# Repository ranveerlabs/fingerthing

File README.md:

# fingerthing

i wanted touchid but not a mac

USB fingerprint security key. npm 2FA first, other FIDO2 sites too.

Pico 2 + pico-fido2 first. UART fingerprint sensor next, then a custom RP2350
board and case. Nothing tested on hardware yet.

[build](firmware/README.md) · [hardware](hardware/DESIGN.md) · [journal](JOURNAL.md)

Targets: Linux, Windows, macOS and [FreeBSD](host/freebsd/README.md).

[AGPL-3.0-only](LICENSE)

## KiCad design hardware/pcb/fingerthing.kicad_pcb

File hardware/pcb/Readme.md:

# pcb

KiCad 10. 34 x 48 mm, four layers, rounded corners. RP2350A, USB-C, R503 header,
GP6 presence button and rear SWD connector. All nets are routed. ERC, DRC and
board/schematic parity pass with no exclusions.

USB targets 90 ohms on JLC04161H-7628. The coupled section uses 0.235 mm traces,
0.15 mm spacing and 0.25 mm clearance to the ground fill. JLCPCB's calculator
returned 0.2347 mm for those inputs on 2026-10-04.

Copper and dielectric thicknesses follow that stackup: 0.035 mm outer copper,
0.0152 mm inner copper, 0.2104 mm prepreg and a 1.065 mm core. Solder-mask and
material-property fields remain nominal. Connector joins and ESD fan-out are
not fully coupled. Final fabrication review and hardware testing remain.

J1 is JAE DX07S016JA1R1500. The local KiCad footprint grounds both shell
reinforcement pads and removes the edge silk markers. Flash, crystal and core
regulator routing come from Raspberry Pi's RP2350A R4/S1 reference. C20 adds a
100 nF VBUS bypass beside the ESD protector's supply via.

R503 cable fit and the enclosure are not confirmed. Do not order this yet.
`bash hardware/check.sh` runs ERC and DRC with KiCad's standard libraries installed.

[BOM](bom.csv): 47 fitted components. R1 is DNP. U2 is AP2112K-3.3TRG1,
with C1 and C5 beside its input and output. Suspend handling and current
measurements remain, see [power](../power.md).

U5 is TPS22919DCKR. GP8 switches both R503 supplies. C21 bypasses the input,
C22 bypasses the output, R15 pulls ON down and R16 pulls sensor RX up to the
switched rail. The `pcb` and `enroll-pcb` images control the switch, with physical
power and backfeed tests still pending.
The UART pull-up branch uses In1.Cu below the USB routing.

The [local switch symbol](fingerthing.kicad_sym) comes from KiCad's
[Power_Management library](https://gitlab.com/kicad/libraries/kicad-symbols/-/blob/master/Power_Management.kicad_sym).
QOD has a passive pin type because TI specifies tying it to OUT. [license](LICENSE.kicad)

[reference](https://datasheets.raspberrypi.com/rp2350/Minimal-KiCAD.zip) · [license](LICENSE.raspberrypi)

[USB footprint](https://gitlab.com/kicad/libraries/kicad-footprints/-/blob/master/Connector_USB.pretty/USB_C_Receptacle_JAE_DX07S016JA1R1500.kicad_mod) · [license](LICENSE.kicad)

[impedance calculator](https://jlcpcb.com/pcb-impedance-calculator) · [stackup](https://jlcpcb.com/impedance) · [ESD layout](https://www.st.com/resource/en/datasheet/usblc6-2.pdf)

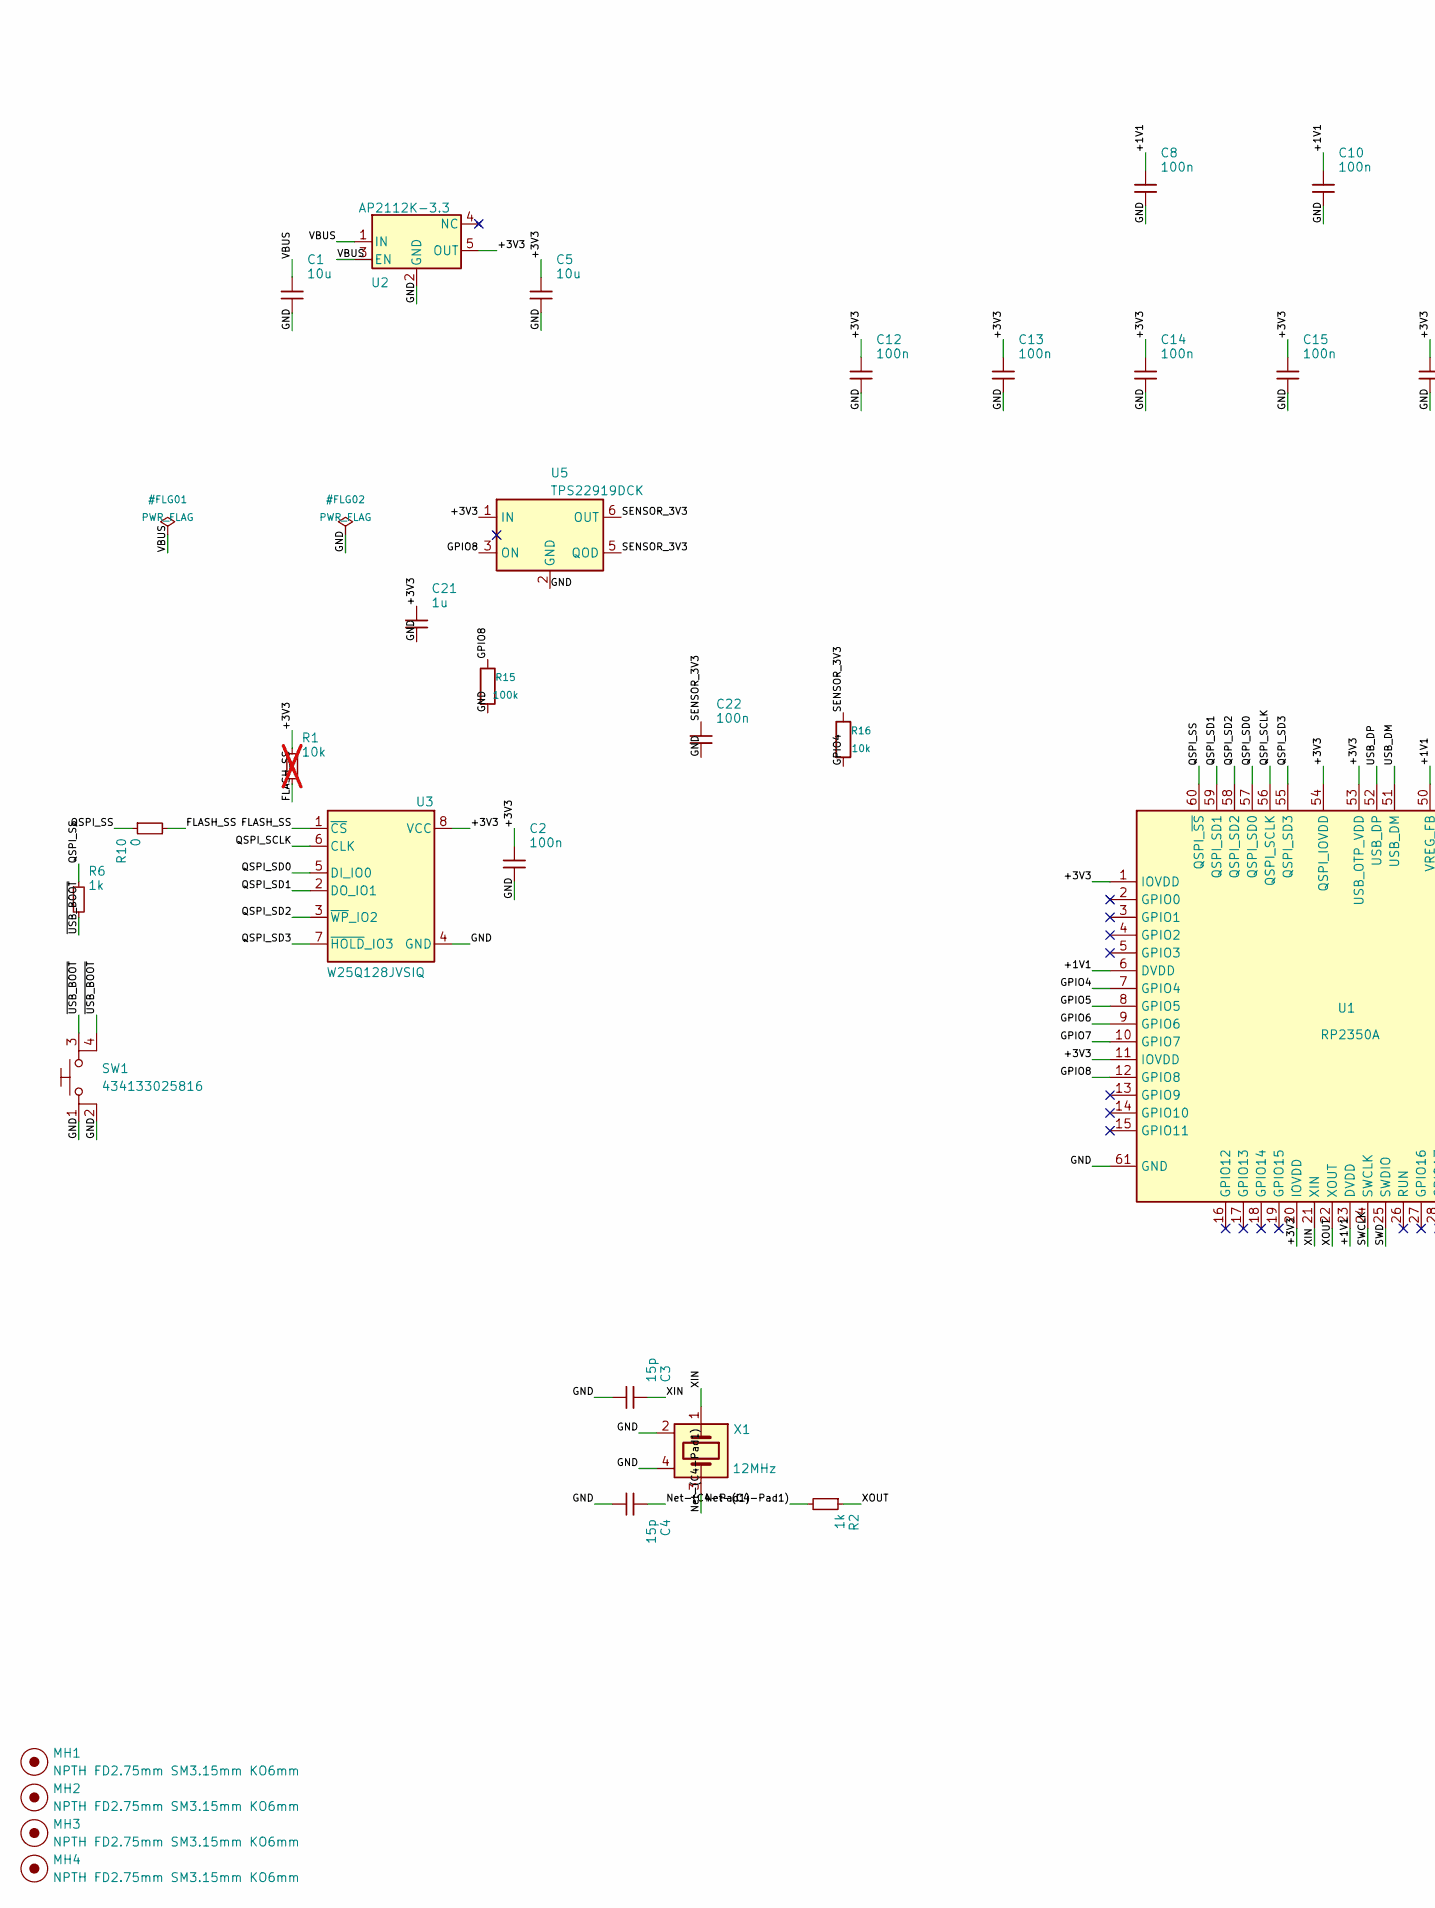
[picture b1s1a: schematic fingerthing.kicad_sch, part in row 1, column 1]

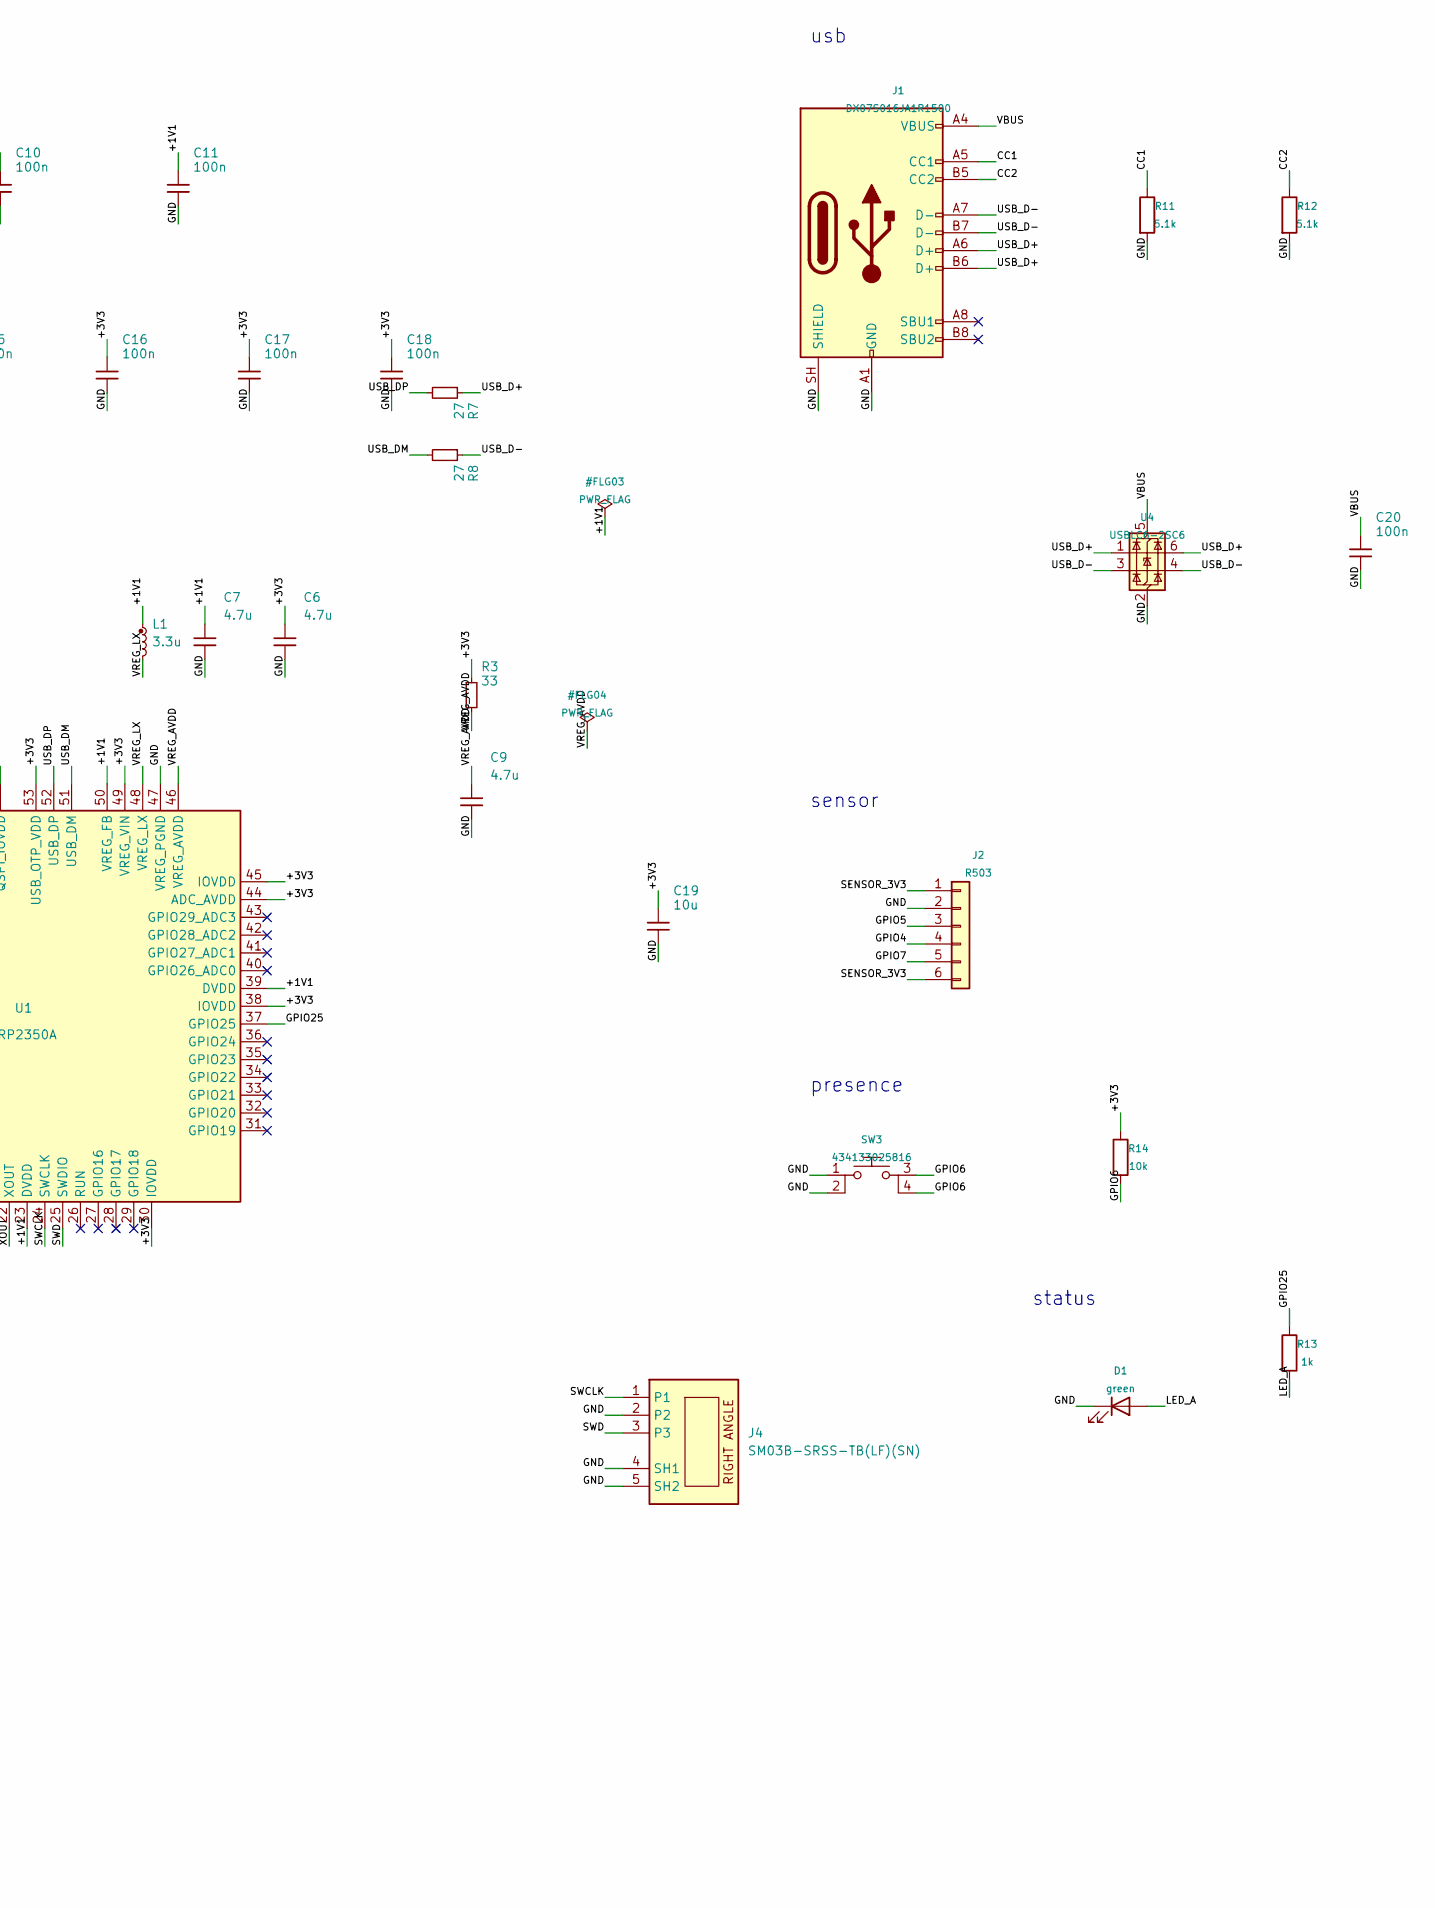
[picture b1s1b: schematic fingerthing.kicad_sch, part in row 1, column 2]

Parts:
C1, C5, C19: 10u; generic_capc2012x125; voltage 16V; tolerance 10%; part_uid RP-01GYSK-AVBE41
C2, C8, C10, C11, C12, C13, C14, C15, C16, C17, C18, C20: 100n; generic_capc1005x50; voltage 25V; tolerance 10%; part_uid RP-01BJ9Y-KRGF41
C3, C4: 15p; generic_capc1005x50; voltage 50V; tolerance 5%; part_uid RP-01C89W-LLY9XV
C6, C7: 4.7u; generic_capc1005x50_wide; voltage 6.3V; tolerance 20%; part_uid RP-019A1P-0C2GHY
C9: 4.7u; generic_capc1005x50; voltage 6.3V; tolerance 20%; part_uid RP-019A1P-0C2GHY
C21: 1u; C_0402_1005Metric; manufacturer_pn C1005X5R1E105K050BC
C22: 100n; generic_capc1005x50; manufacturer_pn GRM155R71E104KE14D
D1: green; LED_0603_1608Metric; manufacturer_pn LTST-C190KGKT
J1: DX07S016JA1R1500; usb-c; manufacturer_pn DX07S016JA1R1500
J2: R503; JST_SH_SM06B-SRSS-TB_1x06-1MP_P1.00mm_Horizontal; manufacturer_pn SM06B-SRSS-TB(LF)(SN)
J4: SM03B-SRSS-TB(LF)(SN); jst_sm03b-srss-tb-lf--sn-; part_uid RP-01EKJ1-8V9SV1
L1: 3.3u; abracon_aota-b201610s3r3-101-t; tolerance 20%; part_uid RP-01GY5D-2VC7WP
MH1, MH2, MH3, MH4: NPTH FD2.75mm SM3.15mm KO6mm; none_mh_npth_fd2p75mm_sm3p15mm_ko6mm; part_uid RP-01HF5R-LCTEJS
R1: 10k; generic_resc1005x35; tolerance 1%; voltage 50V; part_uid RP-019A1P-53DHSX; not fitted
R2, R6: 1k; generic_resc1005x35; tolerance 1%; voltage 50V; part_uid RP-019A1P-4Z6ZWY
R3: 33; generic_resc1005x35; tolerance 1%; voltage 50V; part_uid RP-019A1P-58PW9L
R7, R8: 27; generic_resc1005x35; tolerance 1%; voltage 50V; part_uid RP-01C89V-LTEYC4
R10: 0; generic_resc1005x35; tolerance +50mR; voltage 50V; part_uid RP-019A1P-4Y4V63
R11, R12: 5.1k; R_0402_1005Metric; manufacturer_pn RC0402FR-075K1L
R13: 1k; R_0402_1005Metric; manufacturer_pn RC0402FR-071KL
R14, R16: 10k; R_0402_1005Metric; manufacturer_pn RC0402FR-0710KL
R15: 100k; R_0402_1005Metric; manufacturer_pn RC0402FR-07100KL
SW1: 434133025816; wurthelek_434133025816; part_uid RP-01H0MT-6E9H8F
SW3: 434133025816; wurthelek_434133025816; manufacturer_pn 434133025816
U1: RP2350A; rpi_rp2350a_vias; part_uid RP-01HA9H-9K5E8T
U2: AP2112K-3.3; SOT-23-5; manufacturer_pn AP2112K-3.3TRG1
U3: W25Q128JVSIQ; generic_soic127p790x195-8; voltage 2.7-3.6V; part_uid RP-01JWD4-F1H4N9
U4: USBLC6-2SC6; SOT-23-6; manufacturer_pn USBLC6-2SC6
U5: TPS22919DCK; SOT-363_SC-70-6; manufacturer_pn TPS22919DCKR
X1: 12MHz; generic_xtalcc320x250x80-4; tolerance 30ppm; part_uid RP-01G8X7-GS352B

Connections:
/+1V1: C7.1, C8.1, C10.1, C11.1, L1.1, U1.6 (DVDD), U1.23 (DVDD), U1.39 (DVDD), U1.50 (VREG_FB)
/+3V3: C2.1, C5.1, C6.1, C12.1, C13.1, C14.1, C15.1, C16.1, C17.1, C18.1, C19.1, C21.1, R1.1, R3.1, R14.1, U1.1 (IOVDD), U1.11 (IOVDD), U1.20 (IOVDD), U1.30 (IOVDD), U1.38 (IOVDD), U1.44 (ADC_AVDD), U1.45 (IOVDD), U1.49 (VREG_VIN), U1.53 (USB_OTP_VDD), U1.54 (QSPI_IOVDD), U2.5 (OUT), U3.8 (VCC), U5.1 (IN)
/CC1: J1.A5 (CC1), R11.1
/CC2: J1.B5 (CC2), R12.1
/FLASH_SS: R1.2, R10.2, U3.1 (~CS)
/GND: C1.2, C2.2, C3.2, C4.2, C5.2, C6.2, C7.2, C8.2, C9.2, C10.2, C11.2, C12.2, C13.2, C14.2, C15.2, C16.2, C17.2, C18.2, C19.2, C20.2, C21.2, C22.2, D1.1 (K), J1.A1 (GND), J1.A12 (GND), J1.B1 (GND), J1.B12 (GND), J1.SH (SHIELD), J2.2, J4.2, J4.4 (SH1), J4.5 (SH2), R11.2, R12.2, R15.2, SW1.1, SW1.2, SW3.1, SW3.2, U1.47 (VREG_PGND), U1.61 (GND), U2.2 (GND), U3.4 (GND), U4.2 (GND), U5.2 (GND), X1.2, X1.4
/GPIO4: J2.4, R16.2, U1.7 (GPIO4)
/GPIO5: J2.3, U1.8 (GPIO5)
/GPIO6: R14.2, SW3.3, SW3.4, U1.9 (GPIO6)
/GPIO7: J2.5, U1.10 (GPIO7)
/GPIO8: R15.1, U1.12 (GPIO8), U5.3 (ON)
/GPIO25: R13.1, U1.37 (GPIO25)
/LED_A: D1.2 (A), R13.2
/Net-(C4-Pad1): C4.1, R2.2, X1.3
/QSPI_SCLK: U1.56 (QSPI_SCLK), U3.6 (CLK)
/QSPI_SD0: U1.57 (QSPI_SD0), U3.5 (DI_IO0)
/QSPI_SD1: U1.59 (QSPI_SD1), U3.2 (DO_IO1)
/QSPI_SD2: U1.58 (QSPI_SD2), U3.3 (~WP_IO2)
/QSPI_SD3: U1.55 (QSPI_SD3), U3.7 (~HOLD_IO3)
/QSPI_SS: R6.1, R10.1, U1.60 (QSPI_~SS)
/SENSOR_3V3: C22.1, J2.1, J2.6, R16.1, U5.5 (QOD), U5.6 (OUT)
/SWCLK: J4.1, U1.24 (SWCLK)
/SWD: J4.3, U1.25 (SWDIO)
/USB_D+: J1.A6 (D+), J1.B6 (D+), R7.1, U4.1 (I/O1), U4.6 (I/O1)
/USB_D-: J1.A7 (D-), J1.B7 (D-), R8.1, U4.3 (I/O2), U4.4 (I/O2)
/USB_DM: R8.2, U1.51 (USB_DM)
/USB_DP: R7.2, U1.52 (USB_DP)
/VBUS: C1.1, C20.1, J1.A4 (VBUS), J1.A9 (VBUS), J1.B4 (VBUS), J1.B9 (VBUS), U2.1 (IN), U2.3 (EN), U4.5 (VBUS)
/VREG_AVDD: C9.1, R3.2, U1.46 (VREG_AVDD)
/VREG_LX: L1.2, U1.48 (VREG_LX)
/XIN: C3.1, U1.21 (XIN), X1.1
/XOUT: R2.1, U1.22 (XOUT)
/~USB_BOOT: R6.2, SW1.3, SW1.4

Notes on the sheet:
usb
sensor
presence
status

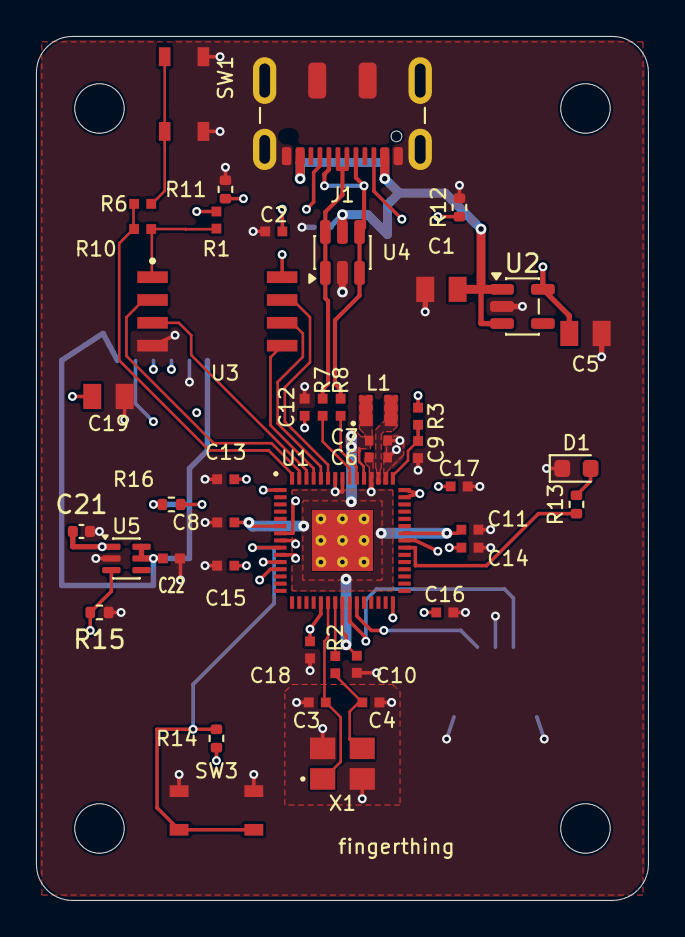
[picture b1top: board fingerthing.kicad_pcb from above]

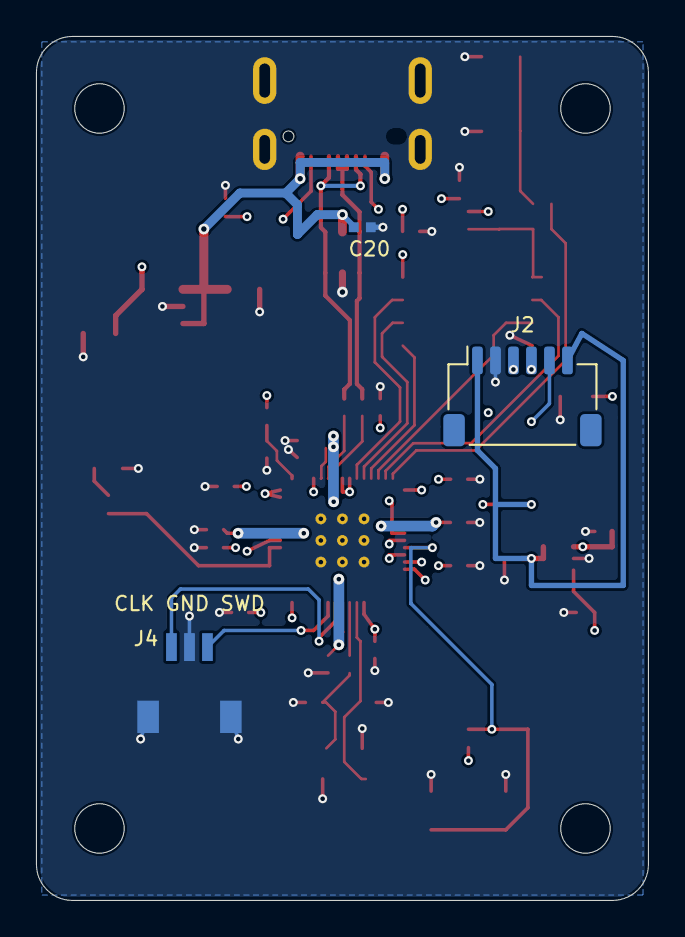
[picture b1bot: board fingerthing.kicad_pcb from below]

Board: 4 copper layers, 34.0 x 48.0 mm, 52 parts (3 on the bottom side), 33 nets.

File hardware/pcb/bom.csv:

"refs","value","manufacturer","mpn","footprint","quantity"
"C1,C5,C19","10u","Murata","GRM21BR61C106KE15L","RPI_COMPILED:generic_capc2012x125","3"
"C2,C8,C10-C18,C20,C22","100n","Murata","GRM155R71E104KE14D","RPI_COMPILED:generic_capc1005x50","13"
"C3,C4","15p","Murata","GRM1555C1H150JA01D","RPI_COMPILED:generic_capc1005x50","2"
"C6,C7","4.7u","Murata","GRM155R60J475ME47D","RPI_COMPILED:generic_capc1005x50_wide","2"
"C9","4.7u","Murata","GRM155R60J475ME47D","RPI_COMPILED:generic_capc1005x50","1"
"C21","1u","TDK","C1005X5R1E105K050BC","Capacitor_SMD:C_0402_1005Metric","1"
"D1","green","Lite-On","LTST-C190KGKT","LED_SMD:LED_0603_1608Metric","1"
"J1","DX07S016JA1R1500","JAE","DX07S016JA1R1500","fingerthing:usb-c","1"
"J2","R503","JST","SM06B-SRSS-TB(LF)(SN)","Connector_JST:JST_SH_SM06B-SRSS-TB_1x06-1MP_P1.00mm_Horizontal","1"
"J4","SM03B-SRSS-TB(LF)(SN)","JST","SM03B-SRSS-TB(LF)(SN)","RPI_COMPILED:jst_sm03b-srss-tb-lf--sn-","1"
"L1","3.3u","Abracon","AOTA-B201610S3R3-101-T","RPI_COMPILED:abracon_aota-b201610s3r3-101-t","1"
"R2,R6","1k","Yageo","RC0402FR-071KL","RPI_COMPILED:generic_resc1005x35","2"
"R3","33","Yageo","RC0402FR-0733RL","RPI_COMPILED:generic_resc1005x35","1"
"R7,R8","27","Yageo","RC0402FR-0727RL","RPI_COMPILED:generic_resc1005x35","2"
"R10","0","Yageo","RC0402JR-070RL","RPI_COMPILED:generic_resc1005x35","1"
"R11,R12","5.1k","Yageo","RC0402FR-075K1L","Resistor_SMD:R_0402_1005Metric","2"
"R13","1k","Yageo","RC0402FR-071KL","Resistor_SMD:R_0402_1005Metric","1"
"R14,R16","10k","Yageo","RC0402FR-0710KL","Resistor_SMD:R_0402_1005Metric","2"
"R15","100k","Yageo","RC0402FR-07100KL","Resistor_SMD:R_0402_1005Metric","1"
"SW1,SW3","434133025816","Wurth Elektronik","434133025816","RPI_COMPILED:wurthelek_434133025816","2"
"U1","RP2350A","Raspberry Pi","RP2350A","RPI_COMPILED:rpi_rp2350a_vias","1"
"U2","AP2112K-3.3","Diodes Incorporated","AP2112K-3.3TRG1","Package_TO_SOT_SMD:SOT-23-5","1"
"U3","W25Q128JVSIQ","Winbond","W25Q128JVSIQ","RPI_COMPILED:generic_soic127p790x195-8","1"
"U4","USBLC6-2SC6","STMicroelectronics","USBLC6-2SC6","Package_TO_SOT_SMD:SOT-23-6","1"
"U5","TPS22919DCK","Texas Instruments","TPS22919DCKR","Package_TO_SOT_SMD:SOT-363_SC-70-6","1"
"X1","12MHz","Abracon","ABM8-272-T3","RPI_COMPILED:generic_xtalcc320x250x80-4","1"
